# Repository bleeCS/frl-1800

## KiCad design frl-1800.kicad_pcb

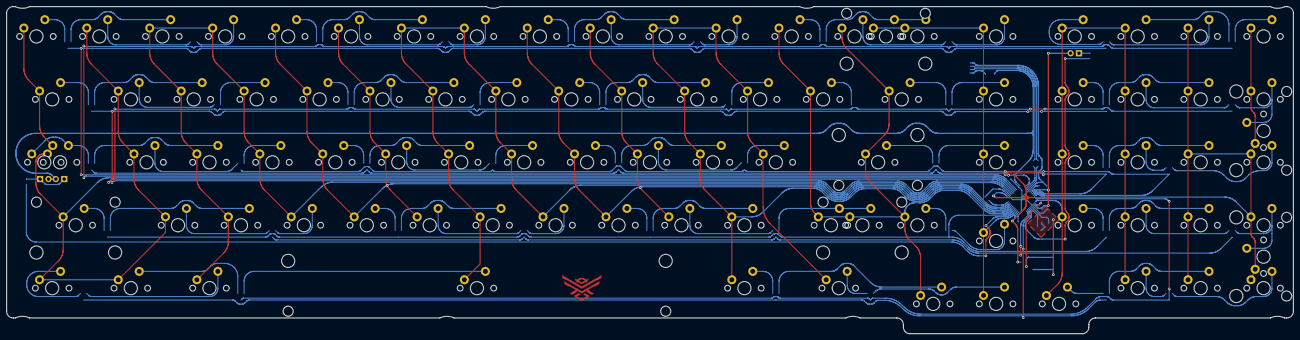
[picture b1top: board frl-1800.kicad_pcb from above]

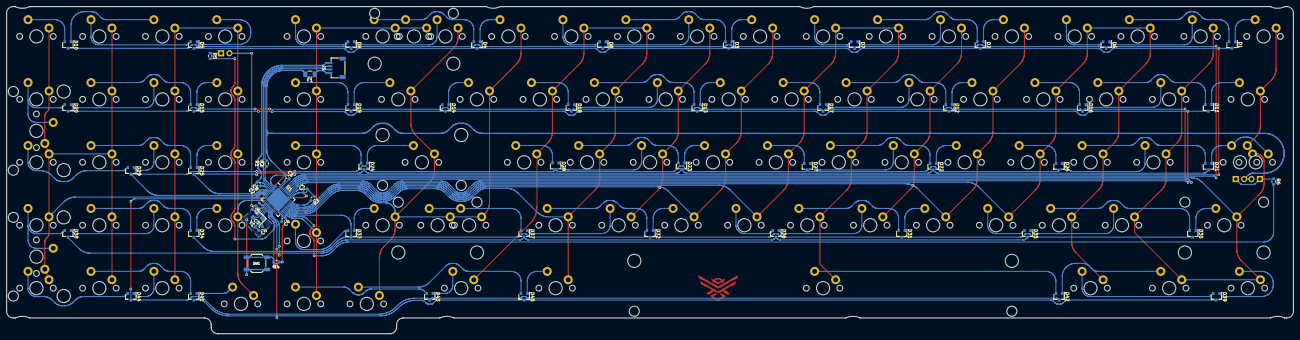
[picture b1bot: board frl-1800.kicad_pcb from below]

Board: 2 copper layers, 389.5 x 99.0 mm, 156 parts (63 on the bottom side), 123 nets.

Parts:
C1: 10uF; C_0603_1608Metric
C2, C3, C4, C5: 0.1uF; C_0603_1608Metric
C6, C7: 22pF; C_0603_1608Metric
C8: 1uF; C_0603_1608Metric
D1, D2, D3, D4, D5, D6, D7, D8, D9, D10, D11, D12, D13, D14, D15, D16, D17, D18, D19, D20, D21, D22, D23, D24, D25, D26, D27, D28, D29, D30, D31, D32, D33, D34, D35, D36, D37, D38, D39, D40, D41, D42, D43, D44: BAV70; SOT-23
F1: 500mA; Fuse_1206_3216Metric
J1: Conn_01x04; JST-SR-4
LOGO1: O-LOGO; MY-LOGO-SVG
MX1, MX2, MX3, MX4, MX5, MX6, MX7, MX8, MX9, MX10, MX11, MX12, MX13, MX15, MX16, MX17, MX19, MX20, MX21, MX23, MX24, MX25, MX26, MX27, MX28, MX29, MX30, MX31, MX32, MX33, MX34, MX36, MX37, MX38, MX39, MX41, MX44, MX45, MX46, MX47, MX48, MX49, MX50, MX51, MX52, MX53, MX54, MX56, MX57, MX58, MX59, MX60, MX62, MX63, MX64, MX65, MX66, MX67, MX68, MX69, MX70, MX71, MX74, MX75, MX76, MX77, MX79, MX80, MX82, MX87, MX88, MX89, MX90, MX91, MX92: MX-NoLED; MXOnly-1U-NoLED
MX14: MX-NoLED; MXOnly-2U-NoLED
MX18: MX-LED; MXOnly-1U
MX22, MX35, MX81, MX83, MX85, MX86: MX-NoLED; MXOnly-1.5U-NoLED
MX40, MX78: MX-NoLED; MXOnly-2U-ReversedStabilizers-NoLED
MX42: MX-LED; MXOnly-1.25U-FLIPPED
MX43: MX-LED; MXOnly-1.75U
MX55: MX-NoLED; MXOnly-2.25U-ReversedStabilizers-NoLED
MX61: MX-NoLED; MXOnly-2.25U-NoLED
MX72: MX-NoLED; MXOnly-1.75U-NoLED
MX73: MX-NoLED; MXOnly-2.75U-NoLED
MX84: MX-NoLED; MXOnly-7U-ReversedStabilizers-NoLED
R1, R2: 22; R_0603_1608Metric
R3, R4: 10k; R_0603_1608Metric
R5, R6: 470; R_0603_1608Metric
SW1: SW_Push; K2-1187SQ-A4SW-06
U1: ATmega32U4-MU; QFN-44-1EP_7x7mm_P0.5mm_EP5.2x5.2mm
Y1: 16MHz; Crystal_SMD_3225-4Pin_3.2x2.5mm

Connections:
+5V: C1.1, C2.1, C3.1, C4.1, C5.1, F1.2, MX18.3, MX42.3, MX43.3, R4.1, U1.2, U1.7, U1.14, U1.24, U1.34, U1.44
CAPS: R6.2, U1.26
Col0: MX1.1, MX2.1, MX22.1, MX23.1, MX42.2, MX43.1, MX44.1, MX61.1, MX62.1, MX81.1, MX82.1, U1.39
Col1: MX3.1, MX4.1, MX24.1, MX25.1, MX45.1, MX46.1, MX63.1, MX64.1, MX83.1, U1.36
Col2: MX5.1, MX6.1, MX26.1, MX27.1, MX47.1, MX48.1, MX65.1, MX66.1, U1.32
Col3: MX7.1, MX8.1, MX28.1, MX29.1, MX49.1, MX50.1, MX67.1, MX68.1, MX84.1, U1.31
Col4: MX9.1, MX10.1, MX30.1, MX31.1, MX51.1, MX52.1, MX69.1, MX70.1, U1.30
Col5: MX11.1, MX12.1, MX32.1, MX33.1, MX53.1, MX54.1, MX71.1, MX85.1, MX86.1, U1.29
Col6: MX13.1, MX15.1, MX34.1, MX35.1, MX55.1, MX72.1, MX73.1, MX74.1, MX90.1, U1.28
Col7: MX14.1, MX16.1, MX17.1, MX36.1, MX56.1, MX80.1, MX91.1, U1.25
Col8: MX18.1, MX19.1, MX37.1, MX38.1, MX57.1, MX58.1, MX75.1, MX76.1, MX87.1, MX92.1, U1.12
Col9: MX20.1, MX21.1, MX39.1, MX40.1, MX41.1, MX59.1, MX60.1, MX77.1, MX78.1, MX79.1, MX88.1, MX89.1, U1.10
D1+: R1.1, U1.4
D1-: R2.1, U1.3
D+: J1.3, R1.2
D-: J1.2, R2.2
GND: C1.2, C2.2, C3.2, C4.2, C5.2, C6.2, C7.2, C8.2, J1.4, R3.1, SW1.1, U1.5, U1.15, U1.23, U1.35, U1.43, U1.45, Y1.2, Y1.4
NUM: R5.2, U1.18
unnamed: C8.1, U1.6
unnamed: D1.1, MX1.2
unnamed: D1.2, MX3.2
unnamed: D2.1, MX5.2
unnamed: D2.2, MX7.2
unnamed: D3.1, MX9.2
unnamed: D3.2, MX11.2
unnamed: D4.1, MX13.2
unnamed: D4.2, MX14.2, MX16.2
unnamed: D5.1, MX18.2
unnamed: D5.2, MX20.2
unnamed: D6.1, MX2.2
unnamed: D6.2, MX4.2
unnamed: D7.1, MX6.2
unnamed: D7.2, MX8.2
unnamed: D8.1, MX10.2
unnamed: D8.2, MX12.2
unnamed: D9.1, MX15.2
unnamed: D9.2, MX17.2
unnamed: D10.1, MX19.2
unnamed: D10.2, MX21.2
unnamed: D11.1, MX22.2
unnamed: D11.2, MX24.2
unnamed: D12.1, MX26.2
unnamed: D12.2, MX28.2
unnamed: D13.1, MX30.2
unnamed: D13.2, MX32.2
unnamed: D14.1, MX34.2
unnamed: D15.1, MX37.2
unnamed: D15.2, MX39.2
unnamed: D16.1, MX23.2
unnamed: D16.2, MX25.2
unnamed: D17.1, MX27.2
unnamed: D17.2, MX29.2
unnamed: D18.1, MX31.2
unnamed: D18.2, MX33.2
unnamed: D19.1, MX35.2
unnamed: D19.2, MX36.2
unnamed: D20.1, MX38.2
unnamed: D20.2, MX40.2, MX41.2
unnamed: D21.1, MX42.1, MX43.2
unnamed: D21.2, MX45.2
unnamed: D22.1, MX47.2
unnamed: D22.2, MX49.2
unnamed: D23.1, MX51.2
unnamed: D23.2, MX53.2
unnamed: D24.1, MX55.2
unnamed: D24.2, MX56.2
unnamed: D25.1, MX57.2
unnamed: D25.2, MX59.2
unnamed: D26.1, MX44.2
unnamed: D26.2, MX46.2
unnamed: D27.1, MX48.2
unnamed: D27.2, MX50.2
unnamed: D28.1, MX52.2
unnamed: D28.2, MX54.2
unnamed: D29.1, MX58.2
unnamed: D29.2, MX60.2
unnamed: D30.1, MX61.2
unnamed: D30.2, MX63.2
unnamed: D31.1, MX65.2
unnamed: D31.2, MX67.2
unnamed: D32.1, MX69.2
unnamed: D32.2, MX71.2
unnamed: D33.1, MX74.2
unnamed: D33.2, MX80.2
unnamed: D34.1, MX75.2
unnamed: D34.2, MX77.2
unnamed: D35.1, MX62.2
unnamed: D35.2, MX64.2
unnamed: D36.1, MX66.2
unnamed: D36.2, MX68.2
unnamed: D37.1, MX70.2
unnamed: D37.2, MX72.2, MX73.2
unnamed: D38.1, MX76.2
unnamed: D38.2, MX78.2, MX79.2
unnamed: D39.1, MX81.2
unnamed: D39.2, MX83.2
unnamed: D40.1, MX85.2
unnamed: D40.2, MX90.2
unnamed: D41.1, MX92.2
unnamed: D41.2, MX88.2
unnamed: D42.1, MX82.2
unnamed: D42.2, MX84.2
unnamed: D43.1, MX86.2
unnamed: D43.2, MX91.2
unnamed: D44.1, MX87.2
unnamed: D44.2, MX89.2
unnamed: MX18.4, R5.1
unnamed: MX42.4, MX43.4, R6.1
unnamed: R3.2, U1.33
RESET: R4.2, SW1.2, U1.13
Row0: D1.3, D2.3, D3.3, D4.3, D5.3, U1.41
Row1: D6.3, D7.3, D8.3, D9.3, D10.3, U1.40
Row2: D11.3, D12.3, D13.3, D14.3, D15.3, U1.38
Row3: D16.3, D17.3, D18.3, D19.3, D20.3, U1.37
Row4: D21.3, D22.3, D23.3, D24.3, D25.3, U1.8
Row5: D26.3, D27.3, D28.3, D29.3, U1.9
Row6: D30.3, D31.3, D32.3, D33.3, D34.3, U1.27
Row7: D35.3, D36.3, D37.3, D38.3, U1.20
Row8: D39.3, D40.3, D41.3, U1.19
Row9: D42.3, D43.3, D44.3, U1.11
VCC: F1.1, J1.1
XTAL1: C6.1, U1.17, Y1.1
XTAL2: C7.1, U1.16, Y1.3

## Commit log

2021-08-15 initialize project
2021-08-15 add switch and other keyboard part submodules
2021-08-15 prep footprint libraries
2021-08-17 submodule updates, finish routing, add edge cuts, add logo
